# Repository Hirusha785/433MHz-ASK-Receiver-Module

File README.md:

# 📡 433MHz ASK RF Receiver Module

## 🚀 Overview

**433MHz ASK RF Receiver Module** is a compact open-hardware wireless receiver PCB designed for receiving **433MHz Amplitude Shift Keying signals** in embedded systems, IoT projects, RF learning setups, remote-control decoding experiments, and custom wireless communication applications.

The design includes an antenna input stage, RF tuning section, transistor-based RF front-end, diode-based signal detection, filtering network, and LM358-based analog signal conditioning to provide a usable output signal for microcontrollers, decoder circuits, oscilloscopes, or logic analyzers.

---

## ✨ Key Features

- 📡 433MHz RF signal reception
- 📶 ASK modulation support
- 🧲 Antenna input matching and RF tuning
- ⚡ Diode-based signal detection stage
- 🔺 LM358-based signal amplification and conditioning
- 🧹 RC filtering for noise reduction
- 🔌 Simple VCC, GND, and DATA output interface
- 🧩 Compact custom PCB layout
- 🛠️ Open-hardware design
- 🧪 Suitable for RF testing, learning, and prototyping

---

## 🧠 Technical Description

This module is designed to receive wireless signals in the **433MHz ISM frequency band** using **ASK modulation**.

The incoming RF signal is captured by the antenna and passed through a tuned RF input network. The signal is then processed through the RF front-end stage, detected using diode-based rectification, filtered using resistor-capacitor networks, and conditioned using LM358 operational amplifier stages.

The final output can be connected to a microcontroller GPIO pin, oscilloscope, logic analyzer, decoder circuit, or embedded system for further processing.

---

## 🧱 System Block Diagram

```text
Antenna
   ↓
RF Input Matching / Tuning
   ↓
RF Front-End Stage
   ↓
ASK Signal Detection
   ↓
Noise Filtering
   ↓
LM358 Signal Conditioning
   ↓
DATA Output
   ↓
Microcontroller / Decoder / Logic Analyzer
```

---

## 🔌 Pinout

| Pin | Name | Description |
|---|---|---|
| 1 | VCC | Power input |
| 2 | DATA | Receiver output signal |
| 3 | GND | Ground |

---

## 🧩 Main Components

| Component | Function |
|---|---|
| Antenna | Captures 433MHz RF signals |
| Inductors | RF tuning and filtering |
| Capacitors | Coupling, filtering, and decoupling |
| Diodes | Signal detection |
| Transistor | RF front-end signal handling |
| LM358 | Amplification and analog signal conditioning |
| Resistors | Biasing, gain setting, and filtering |
| Header Pins | External power and signal interface |

---

## ⚙️ Hardware Design Sections

### 1. Antenna Input Section

The antenna input receives the 433MHz RF signal.  
A properly tuned antenna improves sensitivity, stability, and range.

### 2. RF Tuning Section

The LC components are used to tune and filter the received RF signal.  
This section helps improve selectivity around the 433MHz frequency range.

### 3. RF Front-End Section

The transistor stage helps process the weak RF input signal before detection.

### 4. ASK Signal Detection Section

The diode stage detects amplitude changes in the received RF signal and converts them into a lower-frequency signal component.

### 5. Filtering Section

RC filters smooth the detected signal and reduce unwanted RF noise.

### 6. LM358 Signal Conditioning Section

The LM358 operational amplifier stages amplify and condition the detected signal so it can be used by external digital or analog circuits.

### 7. Output Section

The output pin provides the recovered receiver signal for further processing.

---
## 🧪 Testing Methods

You can test this receiver module using:

- Arduino
- ESP32
- STM32
- Raspberry Pi Pico
- Logic analyzer
- Oscilloscope
- 433MHz ASK transmitter
- RF remote control transmitter

Example testing flow:

```text
433MHz ASK Transmitter
        ↓
433MHz ASK Receiver Module
        ↓
Microcontroller GPIO
        ↓
Serial Monitor / Decoder Software
```

---

## 🧑‍💻 Arduino Basic Test Code

```cpp
#define RF_DATA_PIN 2

void setup() {
  Serial.begin(9600);
  pinMode(RF_DATA_PIN, INPUT);
}

void loop() {
  int rfSignal = digitalRead(RF_DATA_PIN);

  Serial.println(rfSignal);

  delay(10);
}
```

---

## 🧑‍💻 ESP32 Basic Test Code

```cpp
#define RF_DATA_PIN 27

void setup() {
  Serial.begin(115200);
  pinMode(RF_DATA_PIN, INPUT);
}

void loop() {
  int signalState = digitalRead(RF_DATA_PIN);

  Serial.println(signalState);

  delay(10);
}
```

---

## 🔬 Oscilloscope Testing

Recommended test points:

| Test Point | Purpose |
|---|---|
| Antenna input | Check received RF activity |
| Detector output | View detected ASK signal |
| LM358 output | Check conditioned output signal |
| DATA pin | Final receiver output |

---

## 🖼️ Project Preview

### Schematic

### PCB Layer

### 3D PCB Render

--- 

## 🛠️ PCB Design Notes

- Keep the antenna trace short.
- Keep the RF input section away from noisy digital signals.
- Use a clean ground reference.
- Place decoupling capacitors close to the LM358 power pins.
- Keep RF tuning components close to the antenna input.
- Avoid sharp trace corners in the RF section.
- Keep signal paths short where possible.
- Use proper spacing between RF, analog, and output sections.
- Test the board with real 433MHz transmitters before finalizing production.

---

## 📡 Antenna Notes

For better range and sensitivity, use a properly sized antenna.

A common quarter-wave antenna length for 433MHz is approximately:

```text
17.3 cm
```

A simple wire antenna can be used for testing, but performance depends on placement, wire quality, ground reference, and surrounding interference.

---

## ⚠️ Important Notes

This module is intended for:

- Educational use
- RF learning
- Prototype development
- Experimental wireless communication
- Embedded hardware testing

RF performance depends on:

- PCB layout
- Antenna design
- Component tolerance
- Power supply noise
- Environmental interference
- Transmitter power
- Distance between transmitter and receiver

This hardware should be tested and certified according to local RF regulations before any commercial deployment.

---

## 👨‍💻 Author

Designed by **Fernando S.M.H.G**

Open-hardware RF receiver project for embedded systems, electronics learning, and wireless communication experiments.

---

## 📜 License

This project is released under the **MIT License**.

You are free to use, modify, improve, and share this project with proper attribution.

---

## ⭐ Support

If this project helps you, consider giving the repository a star.

```text
Made for RF learning, embedded systems, and open-hardware development.
```

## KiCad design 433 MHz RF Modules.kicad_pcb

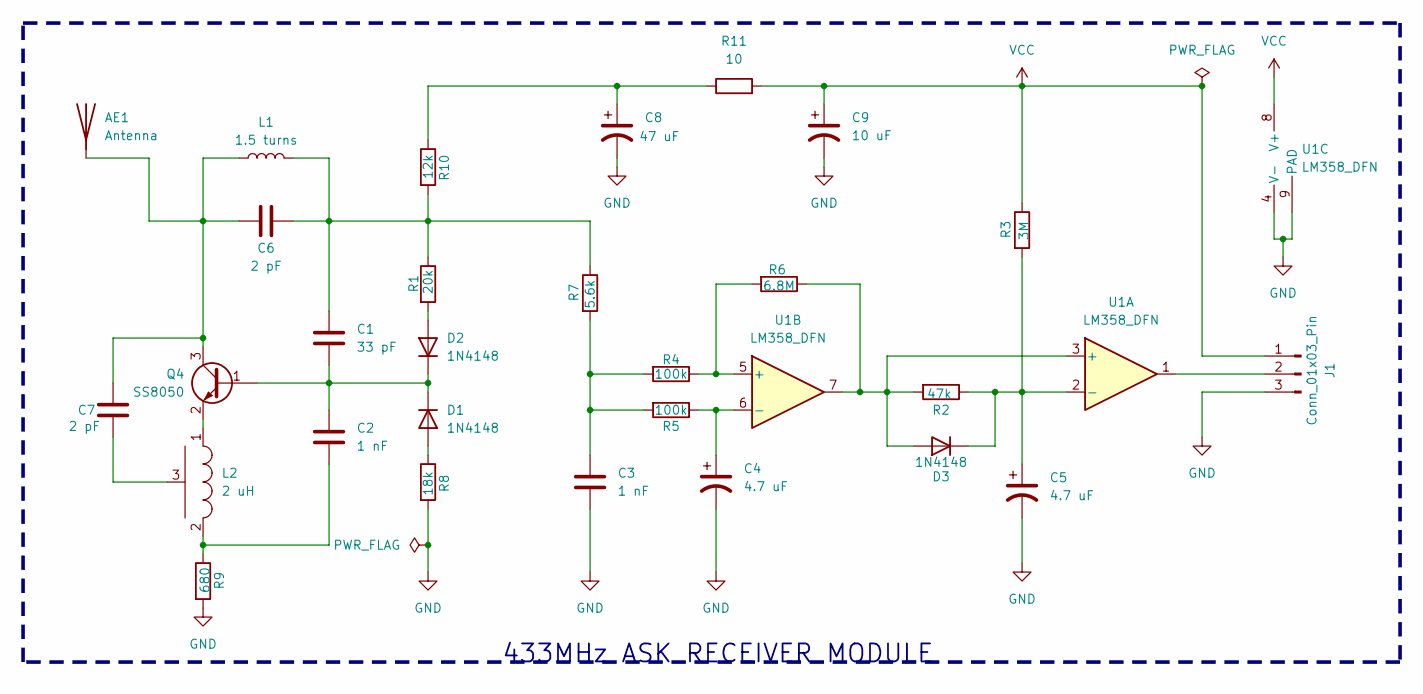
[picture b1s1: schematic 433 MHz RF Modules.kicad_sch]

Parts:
AE1: Antenna; NiceRF_SW868-TH13_868Mhz
C1: 33 pF; C_0805_2012Metric
C2, C3: 1 nF; C_0805_2012Metric
C4, C5: 4.7 uF; C_0805_2012Metric
C6, C7: 2 pF; C_0805_2012Metric
C8: 47 uF; C_0805_2012Metric
C9: 10 uF; C_0805_2012Metric
D1, D2, D3: 1N4148; D_1206_3216Metric
J1: Conn_01x03_Pin; PinHeader_1x03_P2.54mm_Horizontal
L1: 1.5 turns; L_Axial_L5.3mm_D2.2mm_P10.16mm_Horizontal_Vishay_IM-1
L2: 2 uH; Potentiometer_Bourns_3339P_Vertical_HandSoldering
Q4: SS8050; SOT-23
R1: 20k; R_0805_2012Metric
R2: 47k; R_0805_2012Metric
R3: 3M; R_0805_2012Metric
R4: 100k; R_0805_2012Metric
R5: 100k; R_Axial_DIN0411_L9.9mm_D3.6mm_P15.24mm_Horizontal
R6: 6.8M; R_0805_2012Metric
R7: 5.6k; R_0805_2012Metric
R8: 18k; R_0805_2012Metric
R9: 680; R_0805_2012Metric
R10: 12k; R_0805_2012Metric
R11: 10; R_0805_2012Metric
U1: LM358_DFN; DFN-8-1EP_3x3mm_P0.5mm_EP1.66x2.38mm

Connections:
GND: C3.2, C4.2, C5.2, C8.2, C9.2, J1.3, R8.2, R9.2, U1.4 (V-), U1.9 (PAD)
unnamed 1: AE1.1, C6.1, C7.1, L1.1, Q4.3 (C); also elsewhere on the board
unnamed: C1.1, C6.2, L1.2, R1.1, R7.1, R10.2
unnamed: C2.2, L2.2, R9.1
unnamed: C3.1, R4.2, R5.2, R7.2
unnamed: C8.1, R10.1, R11.1
unnamed: D1.2 (A), R8.1
unnamed: C1.2, C2.1, D1.1 (K), D2.1 (K), Q4.1 (B)
unnamed: D2.2 (A), R1.2
unnamed: D3.2 (A), R2.2, R6.1, U1.3 (+), U1.7
unnamed: C5.1, D3.1 (K), R2.1, R3.2, U1.2 (-)
unnamed: J1.2, U1.1
unnamed: C7.2, L2.3 (COMMUN)
unnamed: L2.1, Q4.2 (E)
unnamed: R4.1, R6.2, U1.5 (+)
unnamed: C4.1, R5.1, U1.6 (-)
VCC: C9.1, J1.1, R3.1, R11.2, U1.8 (V+)

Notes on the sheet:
433MHz ASK RECEIVER MODULE

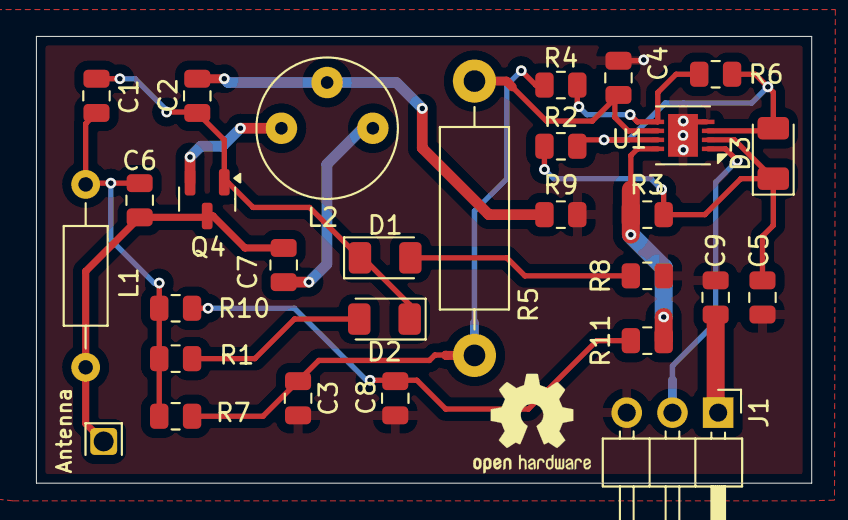
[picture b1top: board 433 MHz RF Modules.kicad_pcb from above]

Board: 4 copper layers, 43.1 x 24.8 mm, 29 parts (0 on the bottom side), 17 nets.

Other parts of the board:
Antenna: Antenna; NiceRF_SW868-TH13_868Mhz

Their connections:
unnamed 1: Antenna.1 (A); also elsewhere on the board

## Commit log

2026-06-14 Revise README for 433MHz ASK RF Receiver Module
    Updated README to provide detailed overview, features, technical description, and project notes for the 433MHz ASK RF Receiver Module.

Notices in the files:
README.md:
License: MIT
